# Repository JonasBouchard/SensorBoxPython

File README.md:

# SensorBox-Python

## Inspired By :
- https://www.printables.com/model/1079858-3d-printer-emission-sensor-array-sensorbox-v2

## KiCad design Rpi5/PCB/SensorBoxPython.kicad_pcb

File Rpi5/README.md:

# SensorBox-Python

## Raspberry Pi 5 pre-configuration

Follow these steps to prepare a Raspberry Pi 5 before running the SensorBox scripts and connecting the sensors.

1. **Update the system**

   ```bash
   sudo apt update
   sudo apt full-upgrade -y
   ```

2. **Install required packages**

   ```bash
   sudo apt install -y python3-pip python3-smbus i2c-tools git
   pip3 install smbus2 gpiozero pyserial flask
   ```

3. **Enable interfaces**

   Launch `raspi-config` and activate the hardware interfaces used by the sensors:

   ```bash
   sudo raspi-config
   ```

   - *Interface Options → I2C* → **Enable**
   - *Interface Options → Serial Port* → **Disable** the login shell and **Enable** the serial hardware

4. **Edit the boot configuration**

   Add the overlays required for I²C bus 0 and for the UART port:

   ```bash
   sudo nano /boot/firmware/config.txt
   ```

   Append the following lines at the end of the file then save:

   ```
   dtoverlay=i2c0
   enable_uart=1
   ```

   Reboot to apply the changes:

   ```bash
   sudo reboot
   ```

5. **Verify I²C bus 0**

   After reboot, ensure that the connected sensors appear on bus 0:

   ```bash
   i2cdetect -y -r 0
   ```

   You should see addresses listed for any devices connected via SDA/SCL.

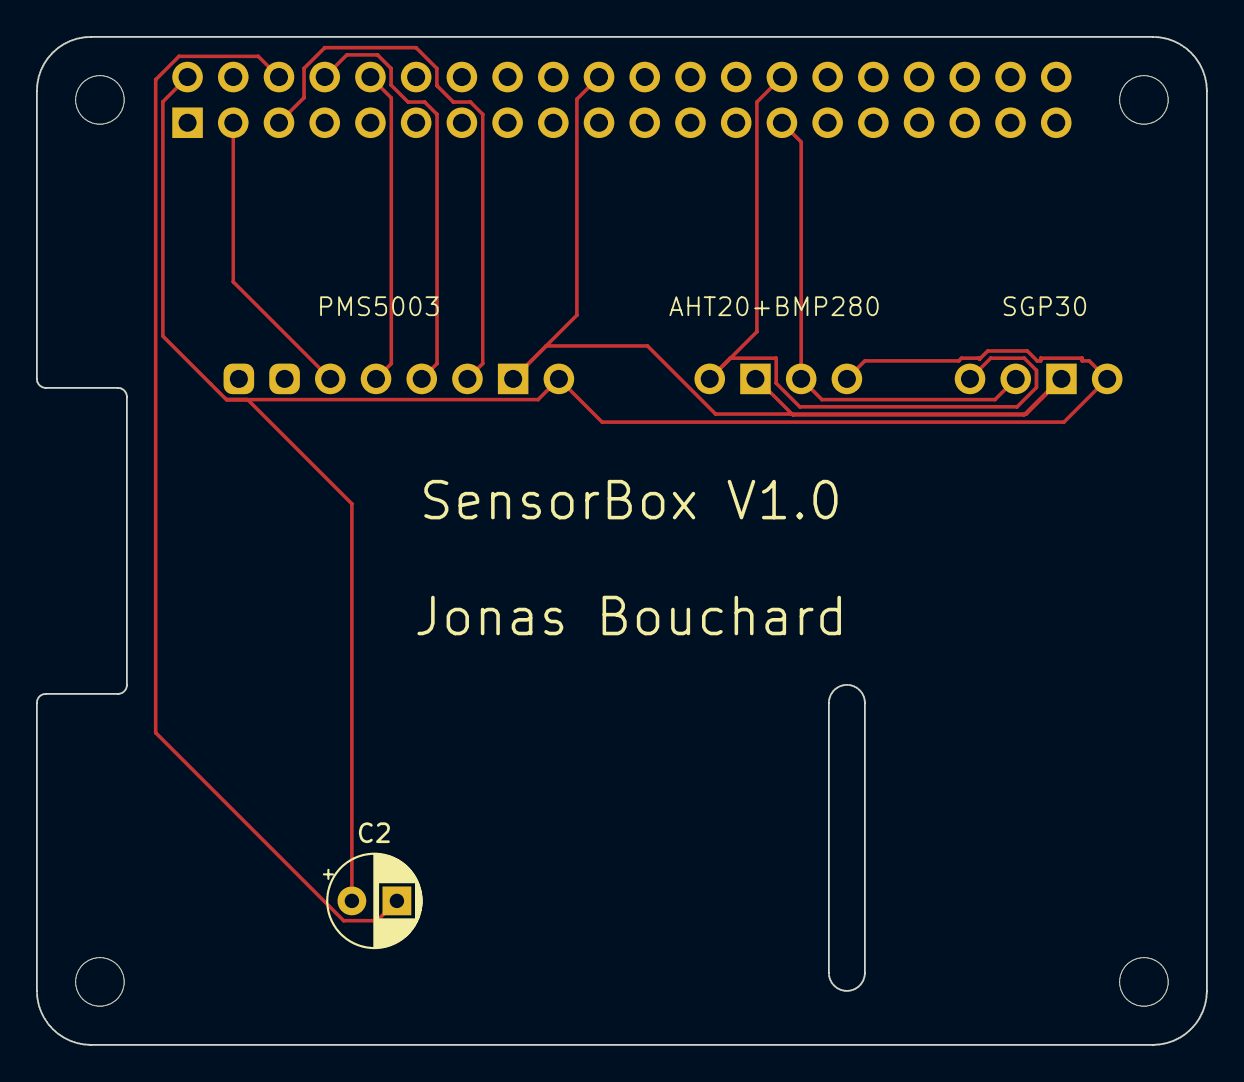
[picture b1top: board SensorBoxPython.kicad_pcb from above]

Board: 2 copper layers, 65.0 x 56.0 mm, 9 parts (1 on the bottom side), 9 nets.

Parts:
AHT20+BMP280: AHT20 + BMP280
C2: C_Polarized; CP_Radial_D5.0mm_P2.50mm
J1: GPIO; PinSocket_2x20_P2.54mm_Vertical
MH1, MH2, MH3, MH4: MountingHole_2.7mm_M2.5
PMS5003: PMS5003
SGP30: SGP30

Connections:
+3V3: J1.1, J1.17
+5V: AHT20+BMP280.1 (VDD), C2.1, J1.2, J1.4, PMS5003.1 (VCC), SGP30.1 (VCC)
/GPIO2/SDA1: J1.3, PMS5003.6 (RST)
/GPIO3/SCL1: J1.5, PMS5003.3 (SET)
/GPIO14/TXD0: J1.8, PMS5003.4 (RXD)
/GPIO15/RXD0: J1.10, PMS5003.5 (TXD)
/ID_SCL: AHT20+BMP280.4 (SCL), J1.28, SGP30.4 (SCL)
/ID_SDA: AHT20+BMP280.2 (SDA), J1.27, SGP30.3 (SDA)
GND: AHT20+BMP280.3 (GND), C2.2, J1.6, J1.9, J1.14, J1.20, J1.25, J1.30, J1.34, J1.39, PMS5003.2 (GND), SGP30.2 (GND)

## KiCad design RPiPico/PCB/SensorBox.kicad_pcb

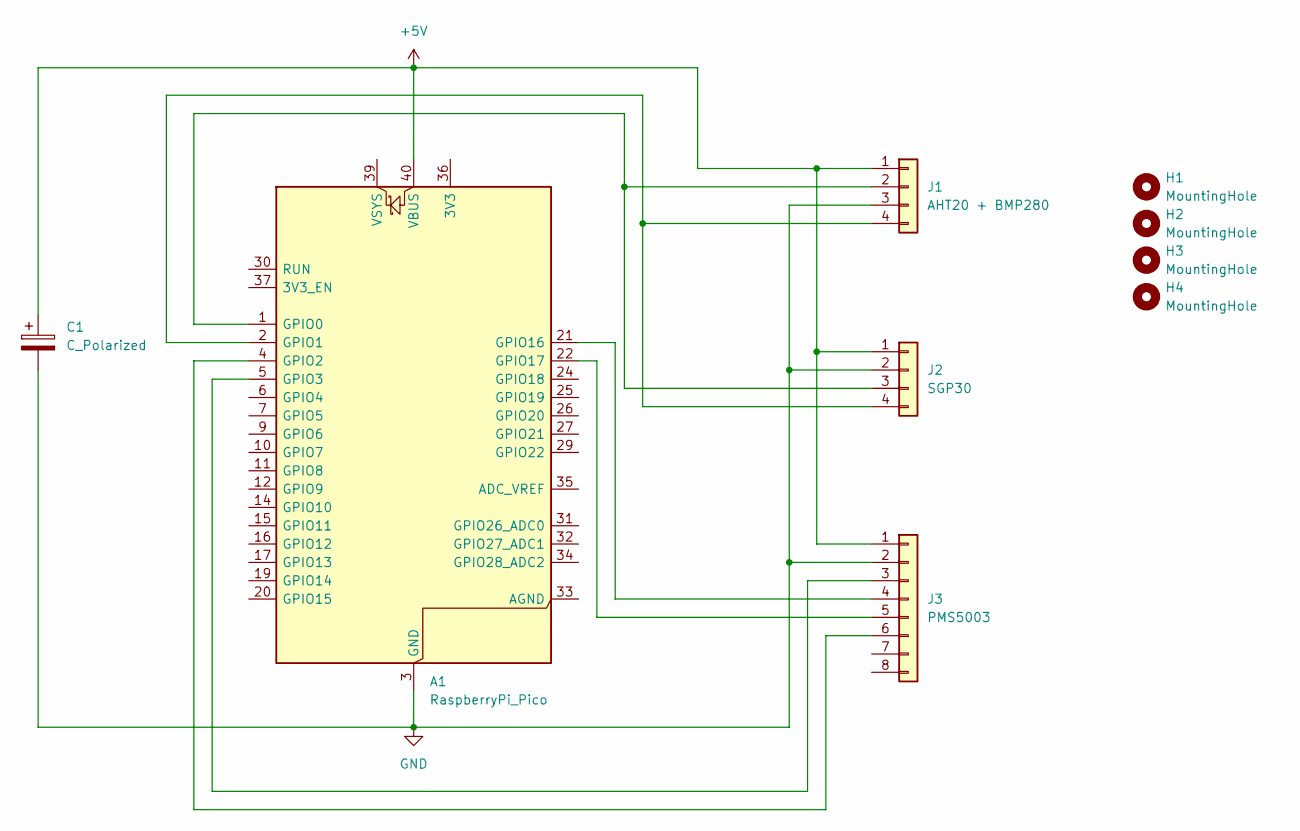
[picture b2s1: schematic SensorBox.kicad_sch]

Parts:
A1: RaspberryPi_Pico; RaspberryPi_Pico_Common_Unspecified
C1: C_Polarized; CP_Radial_D5.0mm_P2.00mm
H1, H2, H3, H4: MountingHole; MountingHole_3.2mm_M3_DIN965_Pad_TopBottom
J1: AHT20 + BMP280
J2: SGP30
J3: PMS5003

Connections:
+5V: A1.40 (VBUS), C1.1, J1.1, J2.1, J3.1
GND: A1.3 (GND), A1.8 (GND), A1.13 (GND), A1.18 (GND), A1.23 (GND), A1.28 (GND), A1.38 (GND), C1.2, J1.3, J2.2, J3.2
unnamed: A1.1 (GPIO0), J1.2, J2.3
unnamed: A1.2 (GPIO1), J1.4, J2.4
unnamed: A1.4 (GPIO2), J3.6
unnamed: A1.5 (GPIO3), J3.3
unnamed: A1.21 (GPIO16), J3.4
unnamed: A1.22 (GPIO17), J3.5

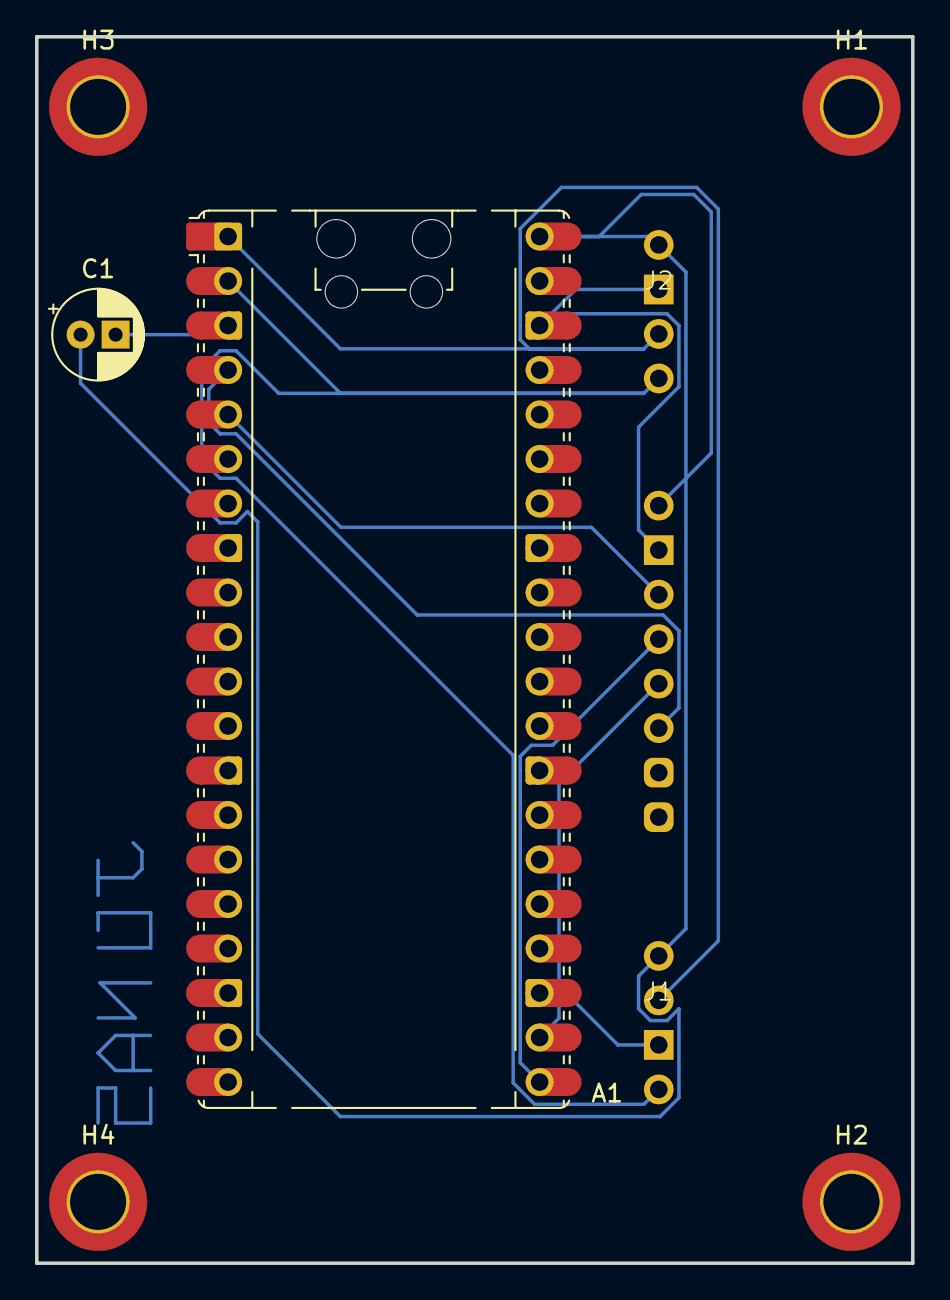
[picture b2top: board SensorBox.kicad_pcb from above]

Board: 2 copper layers, 50.0 x 70.0 mm, 9 parts (0 on the bottom side), 8 nets.

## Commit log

2025-07-16 1st commit
2025-08-14 Move sensor drivers to repo root + update SensorBox.py
2025-08-14 remove unnecessary files
2025-08-14 Add circuit
2025-09-04 WIP: local changes (reorg/deletions)
2025-09-04 RPI5 instaructions
2025-09-04 rename instructions to README
2025-09-04 ajouter i2cdetect aux instructions
2025-09-04 Add aht20+bmp280
2025-09-04 tous les sensors fonctionnent
2025-09-04 Translate Rpi5 SensorBox code comments to English
2025-09-04 remove timeout pms5003
2025-09-04 Add HDMI GUI interface for Pi
2025-09-04 hPa to kPa
2025-09-04 WebUI
2025-09-04 Keep I2C bus open for sensor loop
2025-09-04 Share PMS5003 readings across interfaces
2025-09-04 Better WebUI
2025-09-04 Read sensor data from shared JSON in Tkinter UI
2025-09-04 2 chiffres apres virgule
2025-09-04 Handle SGP30 read errors
2025-09-04 PCB Files
2025-09-04 remove backup pcb files
2025-09-04 Use atmospheric PM data
2025-09-05 step file
2025-09-05 split normal sensors from air quality sensors in web interface
2025-09-06 docs: add Raspberry Pi 5 setup instructions
2025-09-06 Extract HTML template to separate file
2025-09-06 refactor: improve web interface design
2025-09-06 edit box background color
2025-09-06 Highlight readings that exceed thresholds
2025-09-06 style: color hazardous values without warning text
2025-09-06 chore: hide danger label in web ui
2025-09-07 Hide readings for disconnected sensors
2025-09-07 pcb update
2025-09-07 Revert "Hide readings for disconnected sensors"
